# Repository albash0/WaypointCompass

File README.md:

# Waypoint Compass

**An offline GPS navigation device combining sensor integration, embedded UI, and custom PCB design.**

| Navigation interface | Module-carrier design |
| --- | --- |
|  |  |

*Left: a firmware-rendered test fixture using a public business location. Right: a CAD assembly render. Neither image is a photograph or a live navigation measurement.*

Waypoint Compass uses GPS position, a magnetometer, and accelerometer-based tilt compensation to show a target's direction and straight-line distance on a round display. It runs without a phone, Wi-Fi, or an external service. The project spans an earlier OLED prototype, a module-based color version, and a compact integrated PCB design.

A project by [albash0](https://github.com/albash0), a first-year ASEN and CTD student at CU Boulder.

[Engineering notes](docs/ENGINEERING.md) · [Hardware versions](#hardware-versions) · [Build instructions](docs/BUILD.md) · [Controls and wiring](WaypointCompass/README.md) · [Validation](VALIDATION.md)

## About the project

The core problem is making a small navigation display useful when its position, heading, and tilt inputs have different failure modes. The firmware includes calibration, sensor-frame alignment, data-age checks, and visible acquisition/lost-fix states. A target arrow is withheld when the GPS fix is missing or stale.

### My project work

| Area | Work in this project | Source and evidence |
| --- | --- | --- |
| Sensor integration | UART GPS, I²C magnetometer/accelerometer setup, magnetic calibration, frame alignment, and tilt-compensated heading | [SuperMini firmware](WaypointCompass/WaypointCompass.ino), [compact sensor mapping](WaypointCompass/CompactPCB/firmware/WaypointCompassCompact/WaypointCompassCompact.ino) |
| Navigation and interaction | Target bearing/distance, invalid-fix handling, offline nearest-target selection, diagnostics, and a round-screen interface | [Navigation logic](WaypointCompass/BottleNavigation.h), [shared UI](WaypointCompass/BottleUI.h) |
| Hardware design | Modular carrier and a compact four-layer design with onboard sensors and battery power circuitry | [Module carrier](WaypointCompass/PCB/), [C1 design and status](WaypointCompass/CompactPCB/README.md) |
| Verification and tooling | Geographic edge-case tests, real-renderer previews, three firmware builds, and a public-data update script | [Tests](WaypointCompass/tests/), [data updater](WaypointCompass/tools/update_store_list.py), [validation report](VALIDATION.md) |

The project uses TinyGPSPlus, Adafruit display libraries, and KiCad library material. Original contributors and data sources retain their licenses and credits; [third-party notices](THIRD_PARTY.md) describe those boundaries.

### Engineering decisions

- **Use gravity to account for tilt:** align the sensor frames and project magnetic/device-forward vectors onto the horizontal plane when the calibration and input checks permit.
- **Make stale input visible:** missing or outdated GPS data switches the display into an acquisition/lost-fix state.
- **Keep navigation offline:** a small flash-resident target set supports deterministic nearest-target selection without connectivity.
- **Separate software checks from hardware validation:** the compact design compiles, but its electronics still require bench bring-up.

[Read the implementation choices, tradeoffs, and proposed measurements →](docs/ENGINEERING.md)

### Status and validation

| Check | Evidence and limits |
| --- | --- |
| Navigation tests | All **19 public target points**, invalid/stale fixes, and geographic distance edge cases checked under address/undefined-behavior sanitizers. [GitHub Actions](https://github.com/albash0/WaypointCompass/actions). |
| UI | **Eight display states** rendered through actual Adafruit GFX code; examples below. |
| Firmware | SuperMini color, compact C1 color, and earlier OLED versions compiled for the public source release. |
| Module prototype | Documented as the working module-based firmware; publication did not add a new sensor/field test. |
| Compact C1 | Routed schematic/PCB and historical CAD reports are available. **Physical hardware remains unverified.** |
| Open measurements | Absolute heading accuracy, tilt/motion sensitivity, GPS acquisition time, and C1 power/charging behavior remain to be measured. |

Calibration and compilation do not establish a heading-accuracy specification. [Validation details](VALIDATION.md).

### Timeline

These dates come from retained sketch/PCB files and dated update records. They are development milestones, not an imported Git commit history.

| Date | Milestone |
| --- | --- |
| 2026-09-29 | Earliest retained OLED waypoint compass sketch: GPS, QMC5883P heading, calibration and a configurable destination. |
| 2026-09-30 | Round TFT bring-up and signal-pin diagnostics. |
| 2026-10-01 | Modular 60 × 40 mm carrier PCB design retained. |
| 2026-10-02 | Compact C1 integrated 54 × 40 mm four-layer PCB design retained, with onboard sensors and battery power circuitry. |
| 2026-10-16 | Bottle Radar update: nearest-of-19 store selection, shared UI/navigation code, GPS reception details, calibration animation and automated navigation/rendering checks. |
| 2026-11-17 | Public source preparation, removal of private waypoint defaults, and self-contained test dependencies. |

## Hardware versions

| Version | Hardware | Source |
| --- | --- | --- |
| Module-based color prototype | ESP32-S3 SuperMini, GC9A01 round TFT, QMC5883P GY-271, MPU6050 GY-521, UART GPS | [Sketch](WaypointCompass/WaypointCompass.ino), [60 × 40 mm carrier](WaypointCompass/PCB/) |
| Compact C1 prototype | ESP32-S3-MINI-1U-N4R2, LIS2MDL/LIS2DH12, USB-C, battery charging/protection; 54 × 40 mm four-layer PCB | [Firmware and board requirements](WaypointCompass/CompactPCB/README.md) — bench-unverified |
| Earlier OLED waypoint compass | ESP32-S3 SuperMini, SSD1306, QMC5883P, UART GPS; manual target | [Sketch](WaypointCompassOLED/WaypointCompassOLED.ino) |

Read the C1 battery thermistor, polarity, and charging requirements before fabrication or assembly. Supplier reference solids without a local redistribution-license record are omitted; the electrical designs remain editable.

## Interface and application mode

| Acquiring GPS | Calibration |
| --- | --- |
|  |  |

*Host-rendered test states, not live reception or calibration measurements.*

**Bottle Radar** is an application mode that selects the nearest of 19 Boulder retail liquor stores from a dated public city dataset. Manual waypoints are also supported. Distances are straight-line; the device does not provide walking routes, entrance surveys, opening hours, or live closure checks. The embedded data is a **2026-10-16 snapshot** of the [City of Boulder map](https://maps.bouldercolorado.gov/liquor-licenses/).

Private destination defaults are unset. Enter `latitude,longitude` in Serial Monitor at 115200 baud to save a personal target. On the color variants, `NEAREST` restores automatic selection. Calibration and destinations remain on the device. [Full commands, display states and prototype wiring](WaypointCompass/README.md).

## Build and test

[The build guide](docs/BUILD.md) covers the ESP32 core, display/GPS dependencies, and board-specific settings. From the repository root:

```sh
arduino-cli compile --fqbn esp32:esp32:esp32s3:CDCOnBoot=cdc,USBMode=hwcdc,FlashSize=4M --libraries libraries WaypointCompass
sh WaypointCompass/tests/run_tests.sh
```

To refresh the public target dataset, run `python3 WaypointCompass/tools/update_store_list.py`, review the result, and recompile. Both color variants must keep their copied navigation, data, and UI headers synchronized.

## License and credits

Original software, documentation and hardware designs: **GPL-2.0-or-later**, except retained third-party notices. See [LICENSE](LICENSE) and [THIRD_PARTY.md](THIRD_PARTY.md). Adafruit/KiCad material and public city data retain their original notices and applicable publisher terms.

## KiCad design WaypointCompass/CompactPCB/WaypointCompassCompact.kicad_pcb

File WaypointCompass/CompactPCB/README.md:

# Waypoint Compass Compact - C1 prototype

Open `WaypointCompassCompact.kicad_pro` in KiCad 10. The schematic, fully routed PCB and local footprint library are included. This is a new compact design; the working SuperMini/module firmware and original headered carrier remain in their existing folders.

## What is included

- 54 x 40 mm, four-layer, 1.0 mm carrier with the TFT viewing area centered at (27,20) mm.
- Existing inexpensive 7-pin GC9A01 TFT on the front, direct straight male headers and a 2.54 mm board gap.
- Two standard 6 x 6 mm front buttons on the left. Short switches may need case plungers beside the raised display.
- ESP32-S3-MINI-1U-N4R2, LIS2MDL magnetometer and LIS2DH12 accelerometer on the rear. These replace the SuperMini, GY-271 and GY-521 breakout boards. No gyroscope is needed for the current stationary tilt-compensation algorithm.
- USB-C programming and BQ24074 charging with a power path; regulated 3.3 V logic and 5 V TFT/GPS supply; battery protection and a power switch.
- Cable-connected GPS on a JST-SH 4-pin connector. Default 5 V power, selectable 3.3 V; serial signals remain 3.3 V.
- BOM, Gerbers, plated/nonplated drill files, assembly positions, firmware and board documentation.

## Battery and charging

Use a **300-1000 mAh single-cell Li-ion/LiPo intended for 4.2 V charging**. J3 is JST-PH 2-pin: **pin 1 positive, pin 2 cell negative**. Match actual plug polarity; cable colors are not authoritative.

**A separate 10k Semitec 103AT-2 battery thermistor and JST-SH 2-pin cable are required at J5.** Thermally attach the insulated thermistor to the battery. A two-wire battery does not provide this sensor. With J5 empty, charging is inhibited. Charger TS goes to J5 pin 1; J5 pin 2 is system ground. Do not replace the thermistor with a fixed resistor for normal charging.

JP2 open selects about **100 mA**. This is the default for 300-500 mAh cells. Bridge JP2 for about **250 mA** on 500-1000 mAh cells whose manufacturer permits it. For a 1000 mAh cell, use 250 mA mode; at 100 mA it can exceed the charger's timer. Timer is about 9.53 hours nominal, with IC tolerance approximately 7.15-11.92 hours. USB input mode is fixed at 500 mA; the power path reduces charge current when the running load needs the available input current. Switching the device off disables the two regulators while USB charging remains available.

Cell-negative and system GND are separate nets joined by the protection MOSFETs. **Do not wire J3 pin 2 to a system-GND test pad**, because that bypasses protection.

## Build and prototype verification

C1 is a **bench-unverified prototype**. KiCad ERC: 0 violations. PCB DRC: 0 violations, 0 unconnected items and 0 schematic parity issues with the supplied rules; the reports list configured ignored checks. Firmware compiles with ESP32 Arduino core 3.3.8. These checks establish file consistency, not successful hardware operation or charging certification.

Use SMT assembly/reflow for the LGA, QFN, SON and WSON packages. Most passives are 0603; R19/R20 are 0402. Hand solder the front buttons, TFT header and rear JST-PH battery connector. Supply the assembler with BOM, position CSV, native project and component orientation information. Confirm actual MPN availability and permitted substitutions at ordering.

Before using the battery charger, verify power rails, charge current, NTC response, protection behavior, temperature and sensors on the bench. Keep the battery and its cable away from the magnetometer; recalibrate in the final assembled enclosure and check heading while charging.

## Firmware

**2026-10-16 update:** Bottle Radar now selects the nearest of 19 city-listed Boulder retail liquor stores. See `firmware/README.md` for current UI and commands; the build guide describes the original firmware.

Sketch: `firmware/WaypointCompassCompact/WaypointCompassCompact.ino`.

Arduino IDE board: ESP32S3 Dev Module; 4 MB flash; QSPI PSRAM; Hardware CDC/JTAG USB; USB CDC On Boot enabled. Install TinyGPSPlus, Adafruit GFX, Adafruit GC9A01A and their Library Manager dependencies.

- Default mode: nearest city-listed Boulder liquor store. Manual coordinates remain available over USB.
- First startup runs 10-second 3D calibration; rotate the complete device around all axes. Valid calibration is saved across resets.
- CAL button repeats calibration. Holding CAL while resetting enters the USB ROM bootloader; release CAL after entering the bootloader.
- ACTION toggles GPS diagnostics. Serial commands at 115200: `NEAREST`, `STORES`, `DETAILS`, `STATUS`, `NMEA`, `CAL`, `CLEAR`, or `latitude,longitude`.
- GPS defaults to 9600 baud. GPIO44 receives GPS TX; GPIO43 transmits to GPS RX.
- Compact sensor mapping matches rear-mounted C1 footprints. Verify +Z gravity is approximately +1 g with the screen face up, and check compass direction/tilt on the first board.
- Battery voltage in Serial STATUS is an ADC estimate, not a percentage gauge.

Compile command (with arduino-cli installed):

```sh
arduino-cli compile --fqbn esp32:esp32:esp32s3:CDCOnBoot=cdc,USBMode=hwcdc,FlashSize=4M,PSRAM=enabled firmware/WaypointCompassCompact
```

## Public source files

Native KiCad schematic, routed PCB, local symbols/footprints, BOM and unpacked fabrication outputs are included. Supplier 3D references, derived assembly solids, historical ZIPs, prebuilt firmware and local CAD history are omitted. Model paths may refer to omitted visualization assets; they do not affect copper or fabrication. Use the schematic and BOM to review the design.

The native files are the design authority. Development scripts are retained as references; running `build_compact.py --board` regenerates an unrouted board and overwrites the routed layout. Work in a separate copy before regenerating.

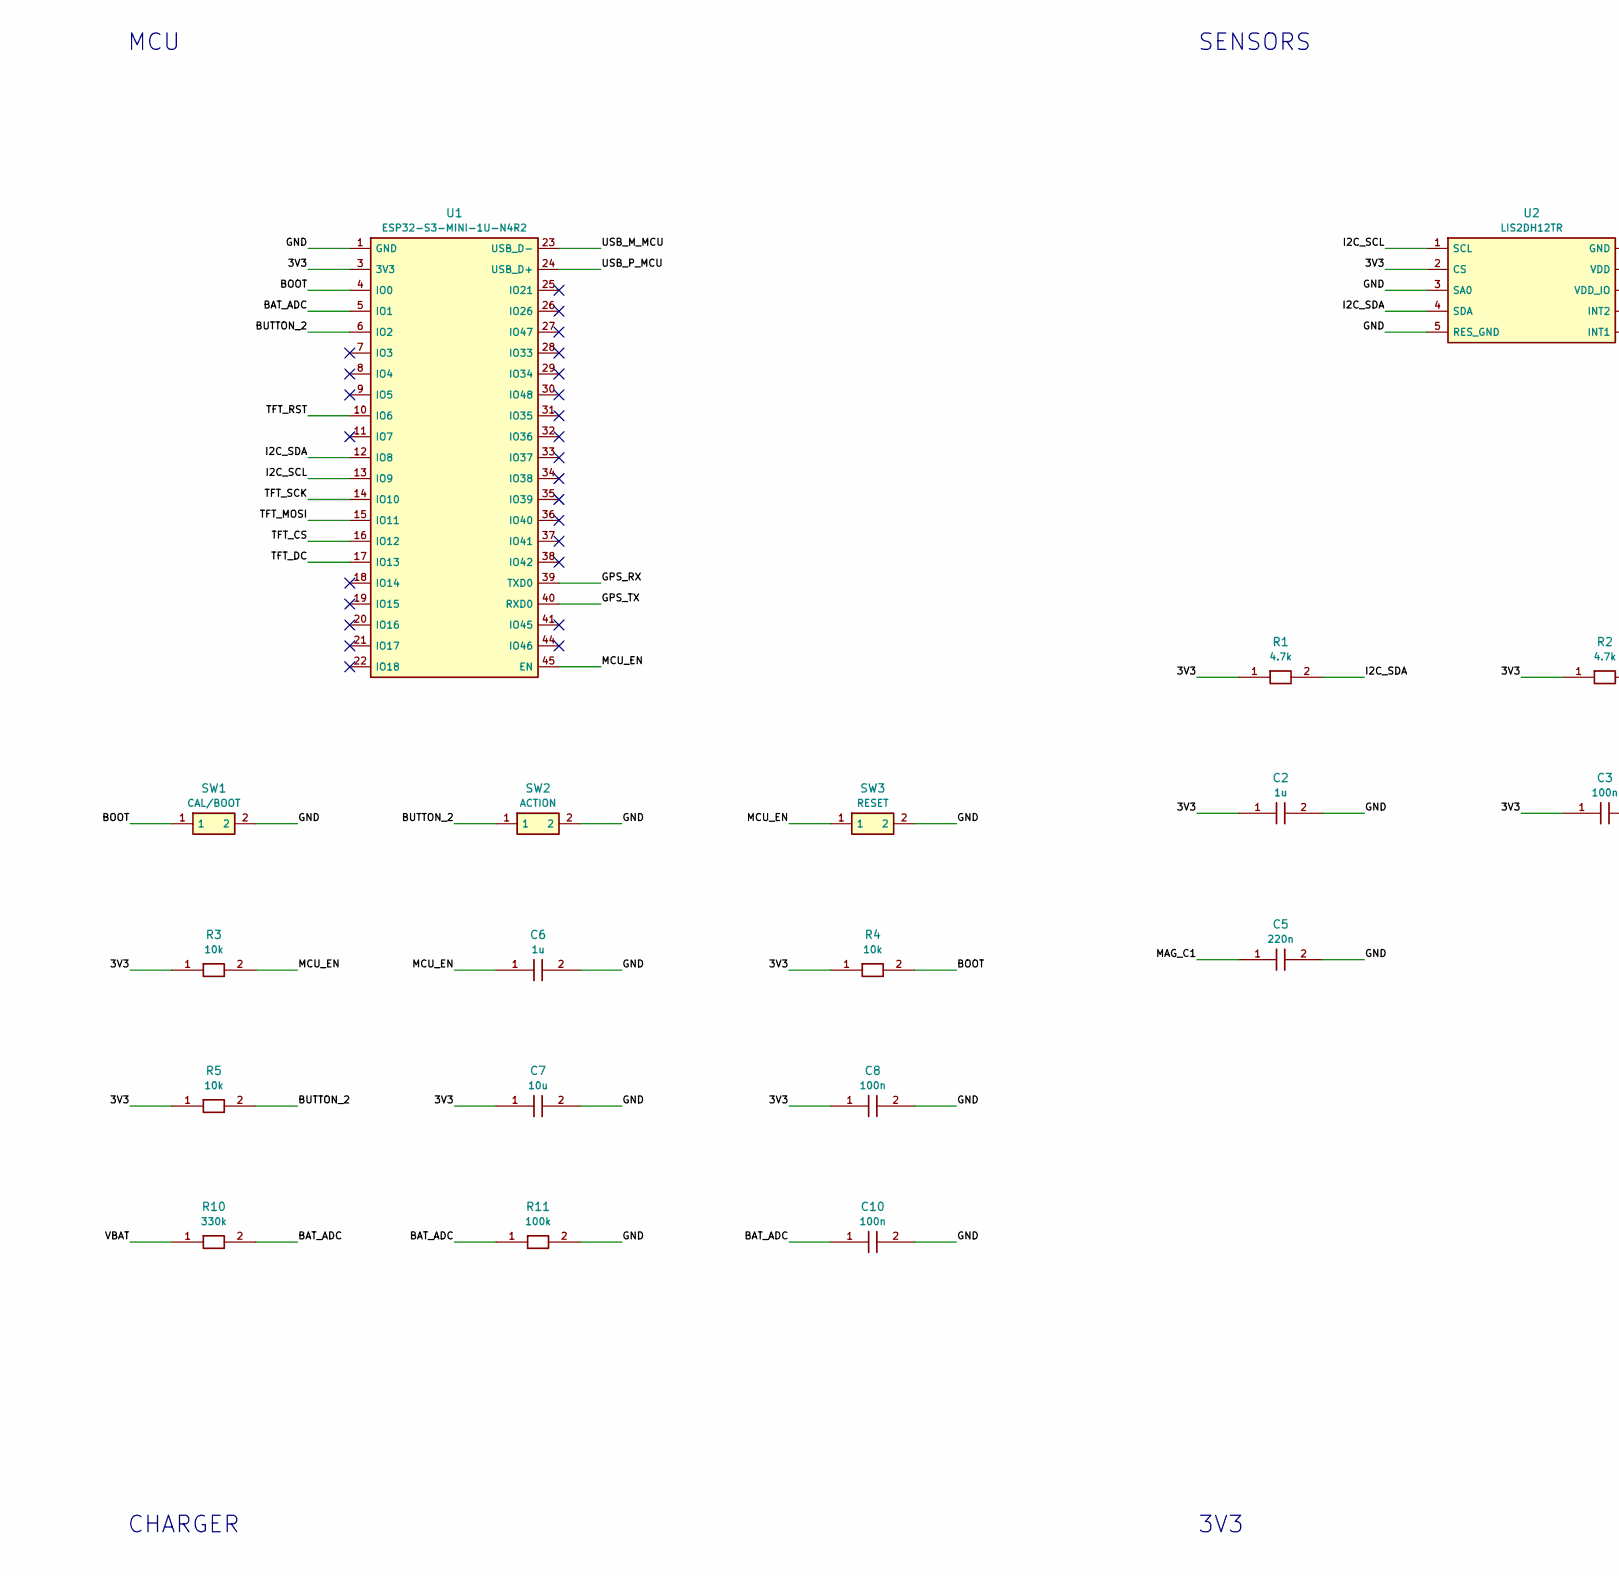
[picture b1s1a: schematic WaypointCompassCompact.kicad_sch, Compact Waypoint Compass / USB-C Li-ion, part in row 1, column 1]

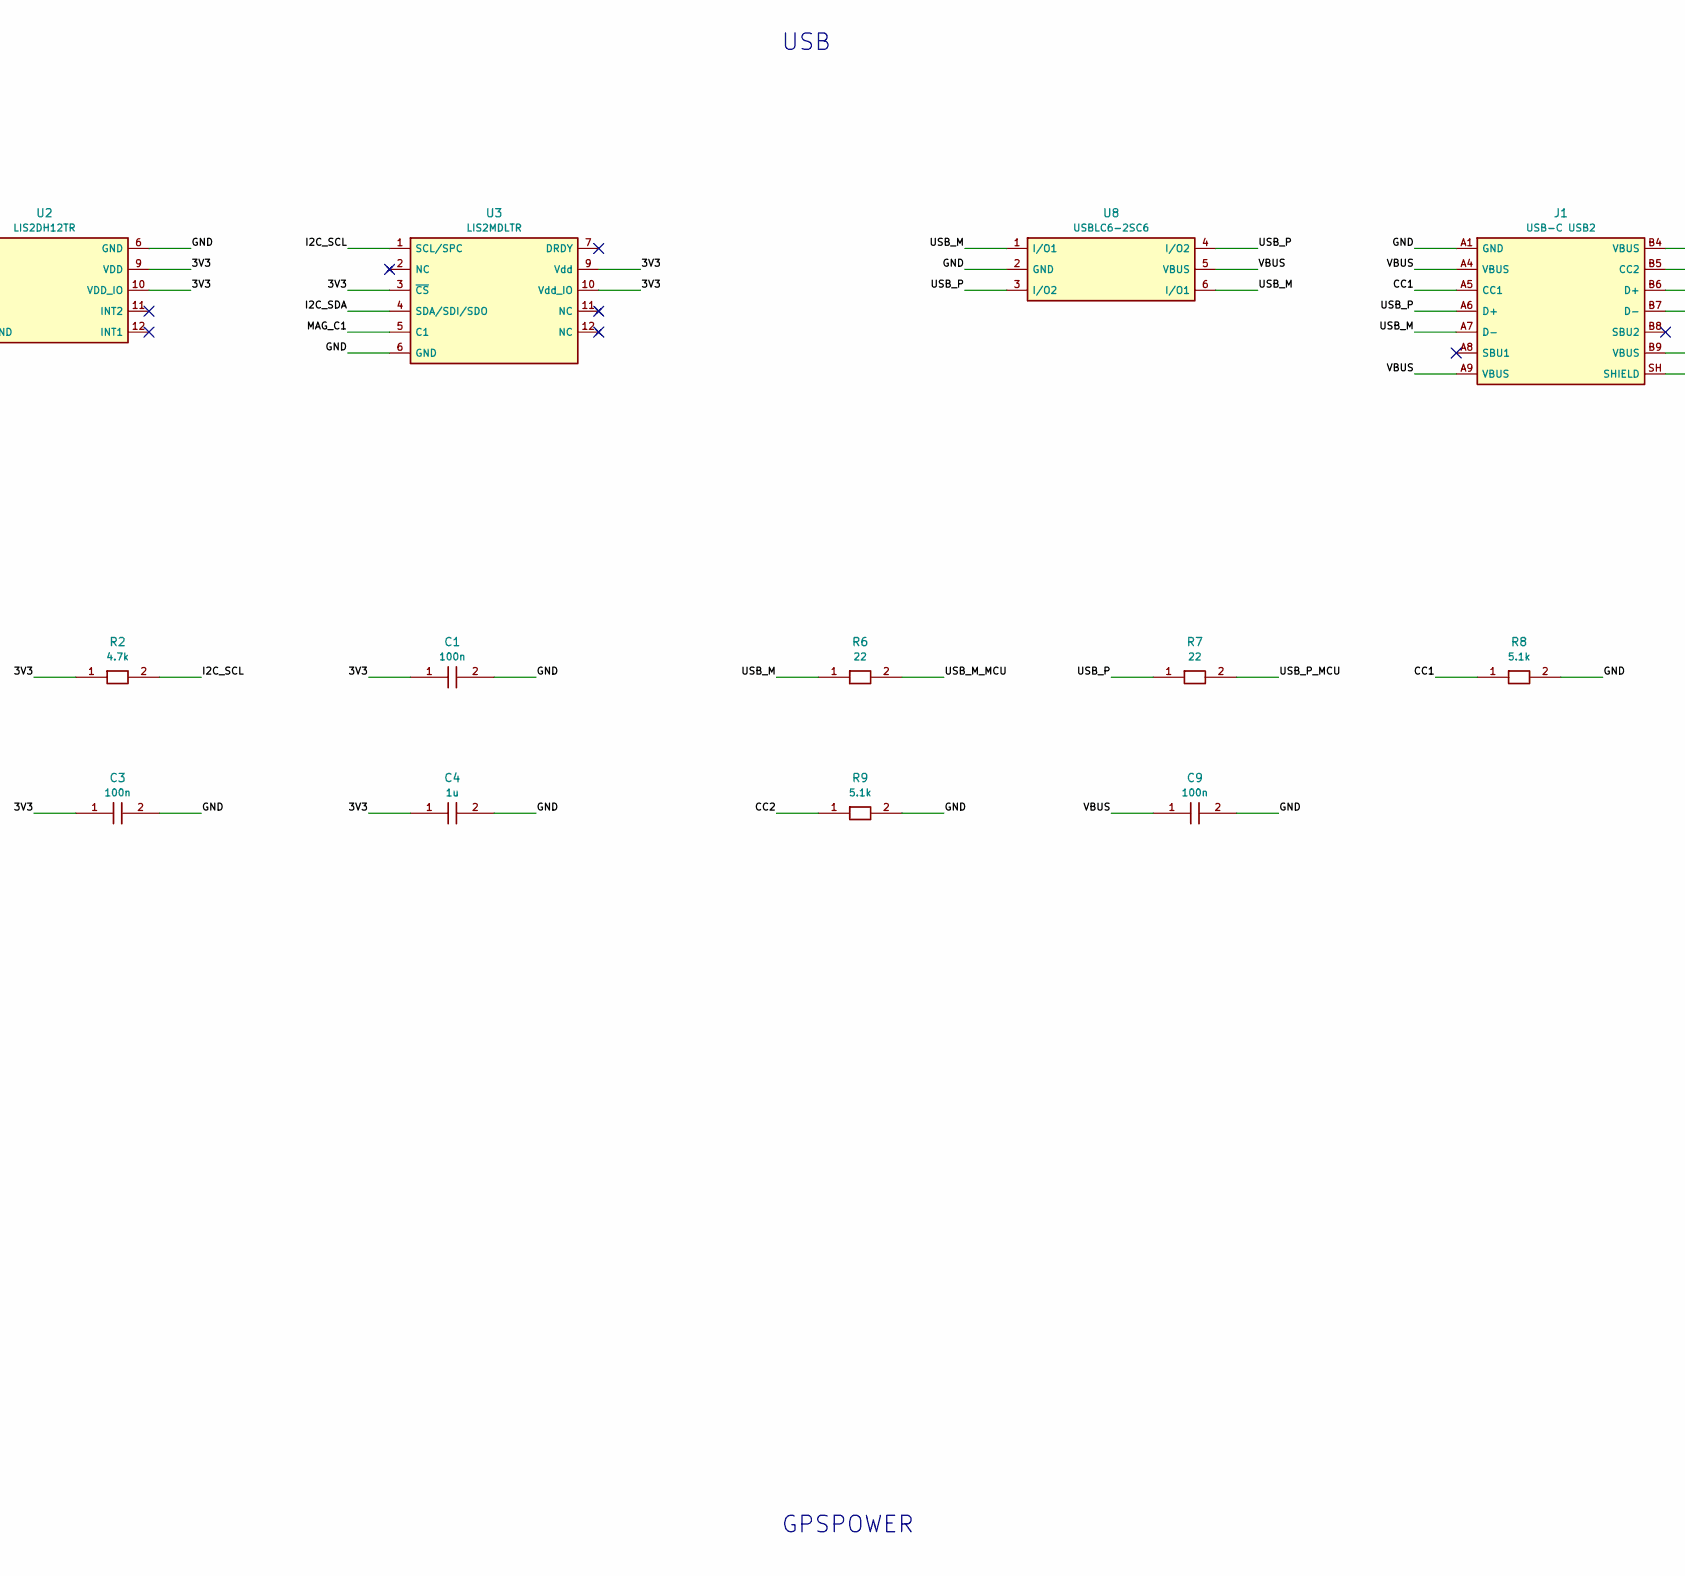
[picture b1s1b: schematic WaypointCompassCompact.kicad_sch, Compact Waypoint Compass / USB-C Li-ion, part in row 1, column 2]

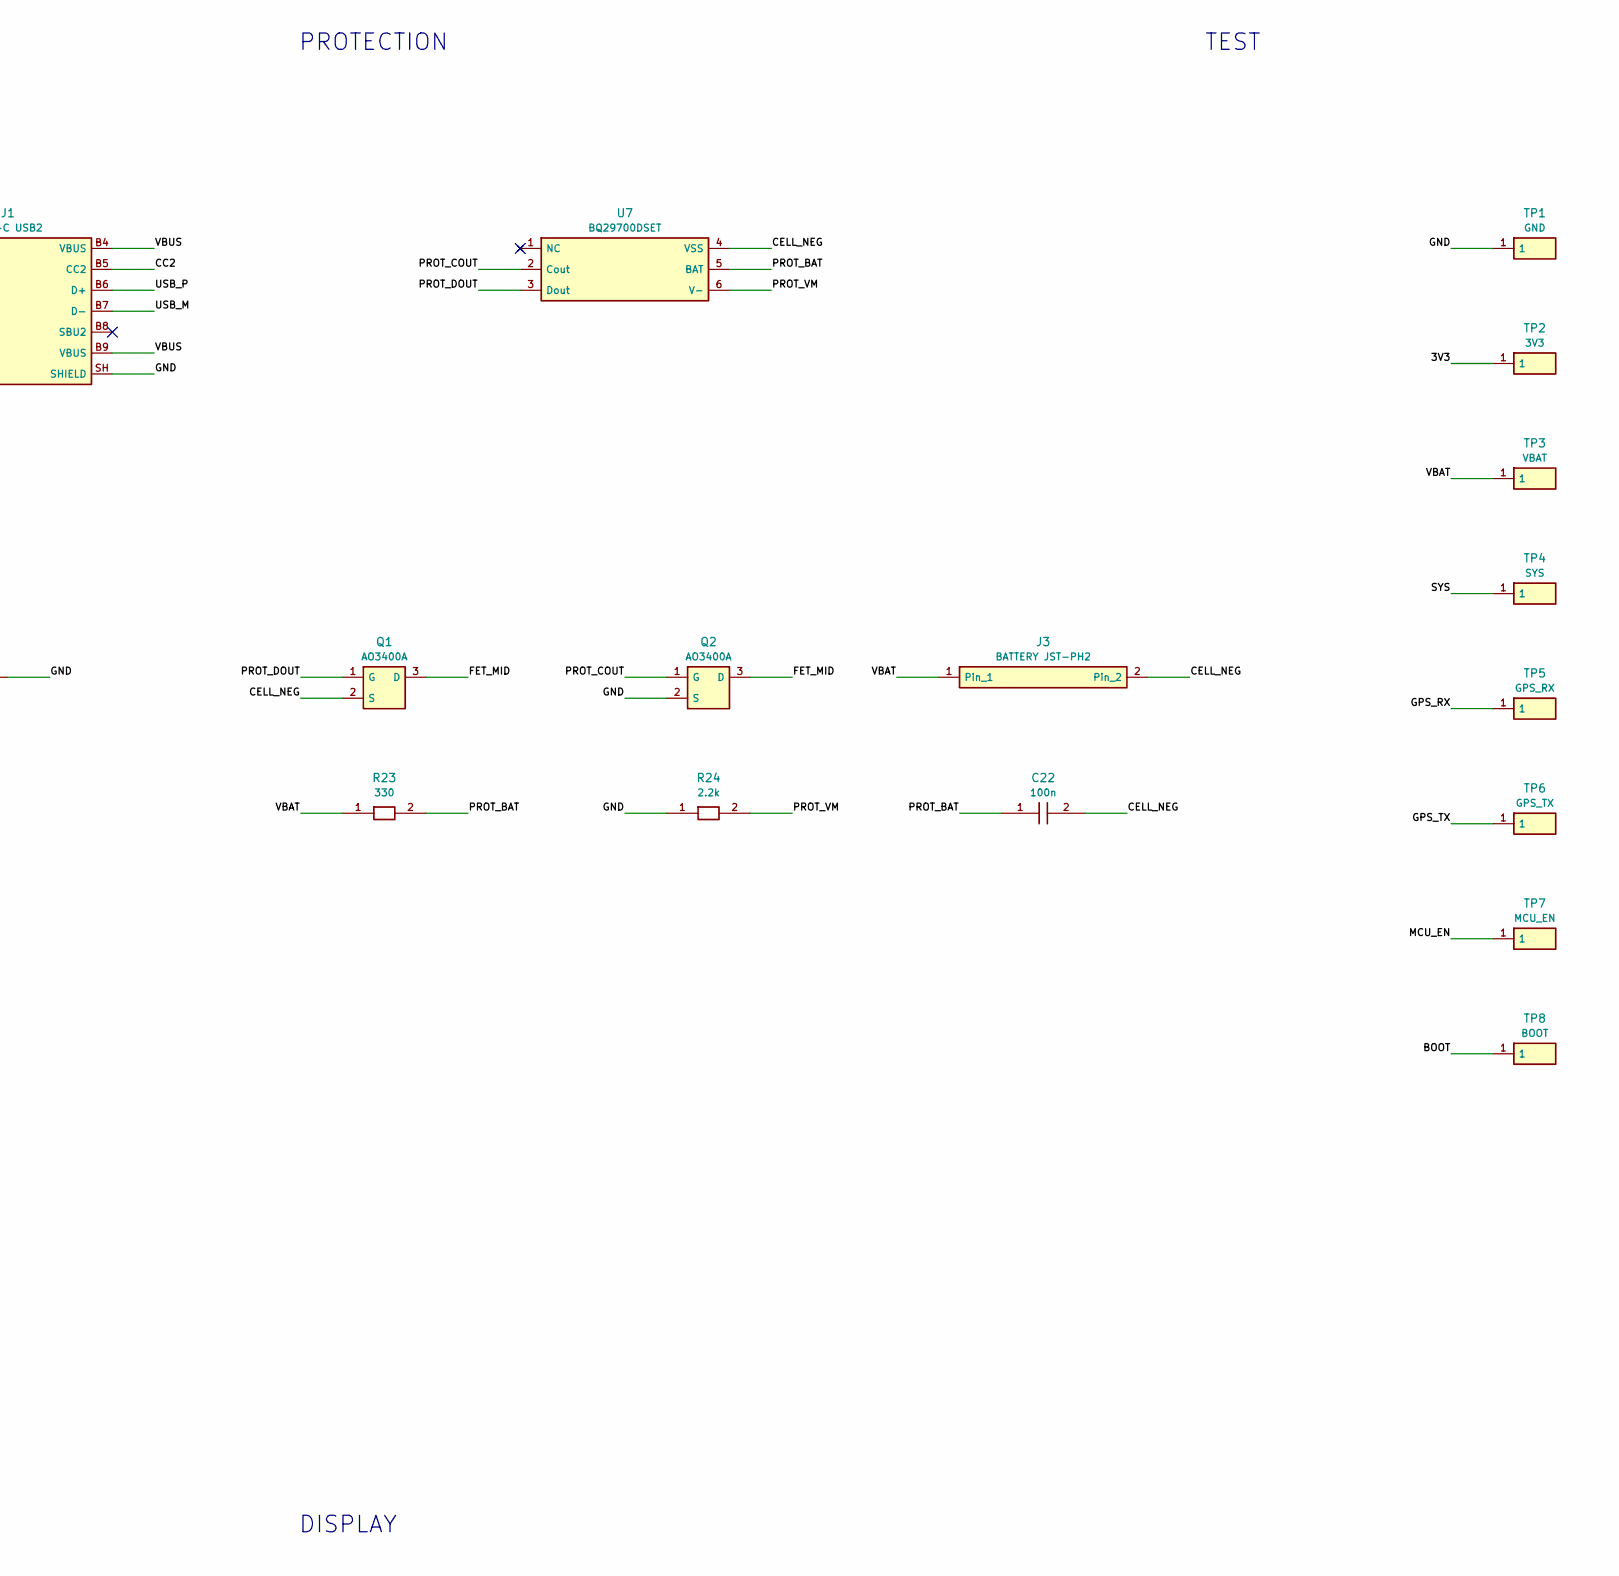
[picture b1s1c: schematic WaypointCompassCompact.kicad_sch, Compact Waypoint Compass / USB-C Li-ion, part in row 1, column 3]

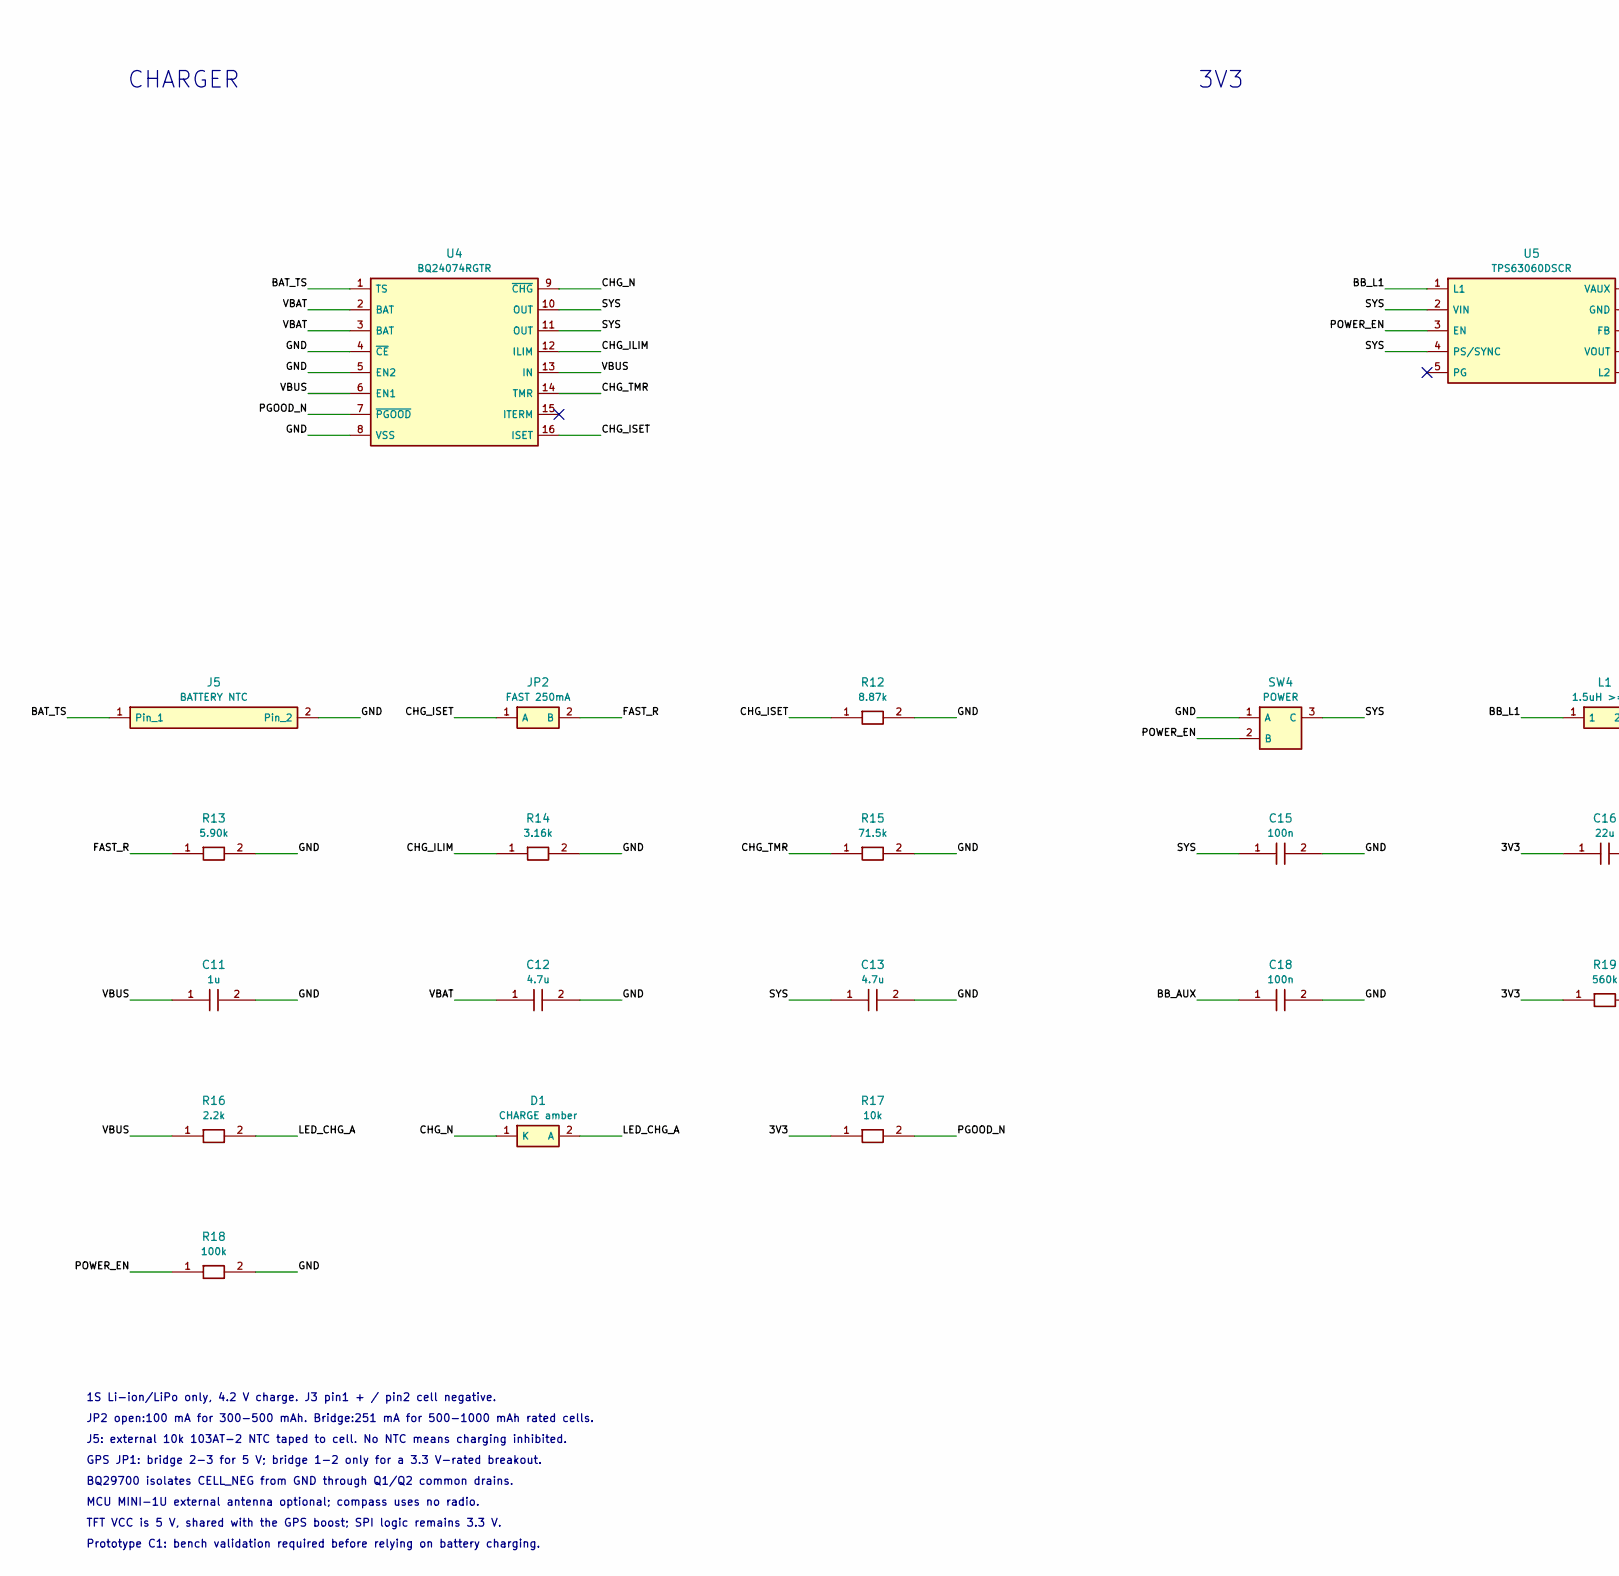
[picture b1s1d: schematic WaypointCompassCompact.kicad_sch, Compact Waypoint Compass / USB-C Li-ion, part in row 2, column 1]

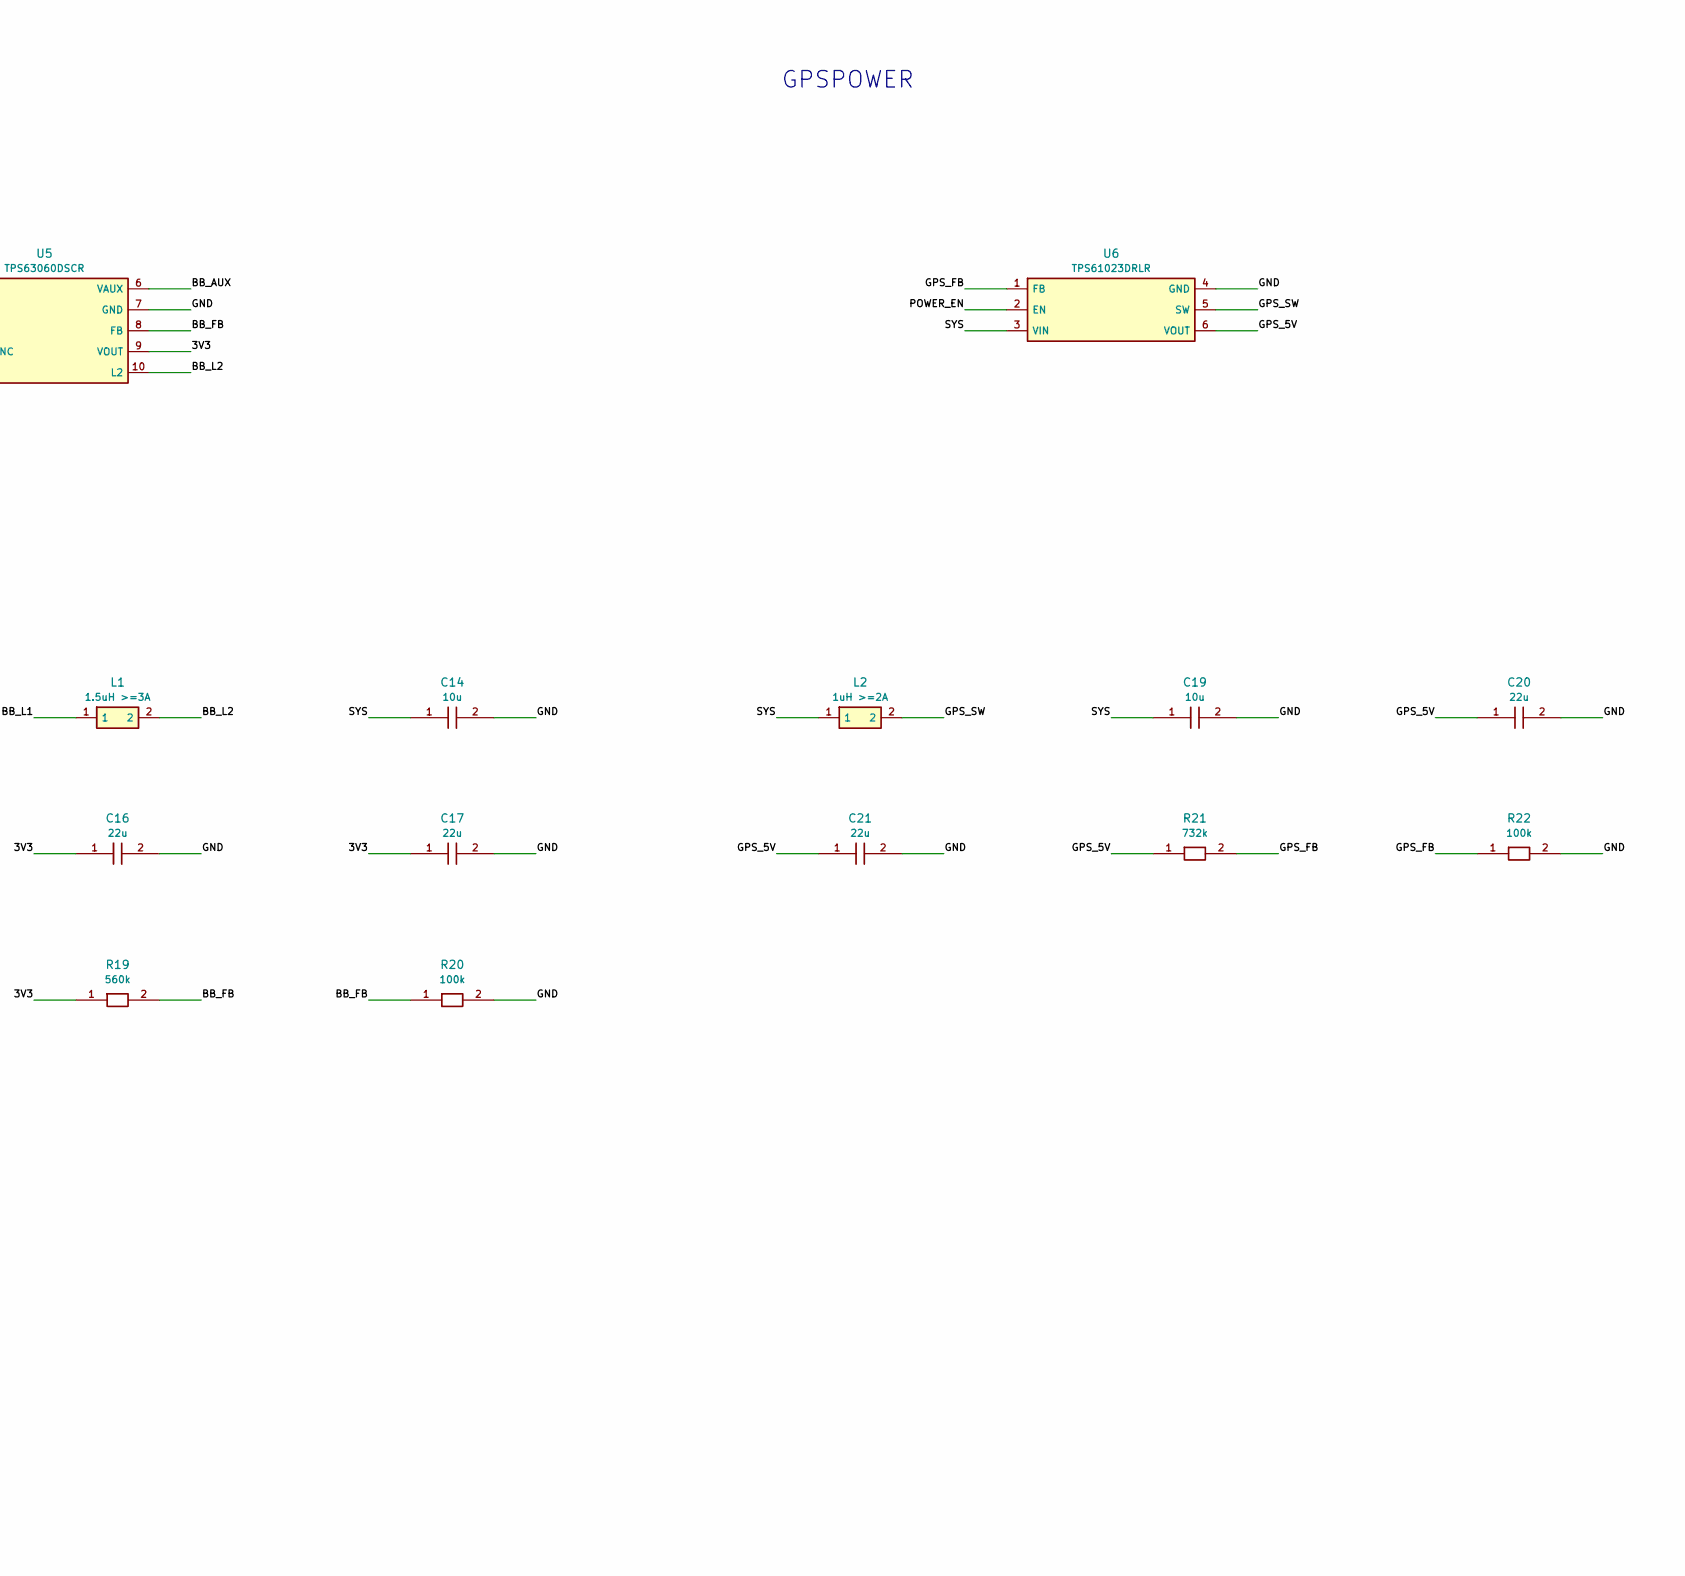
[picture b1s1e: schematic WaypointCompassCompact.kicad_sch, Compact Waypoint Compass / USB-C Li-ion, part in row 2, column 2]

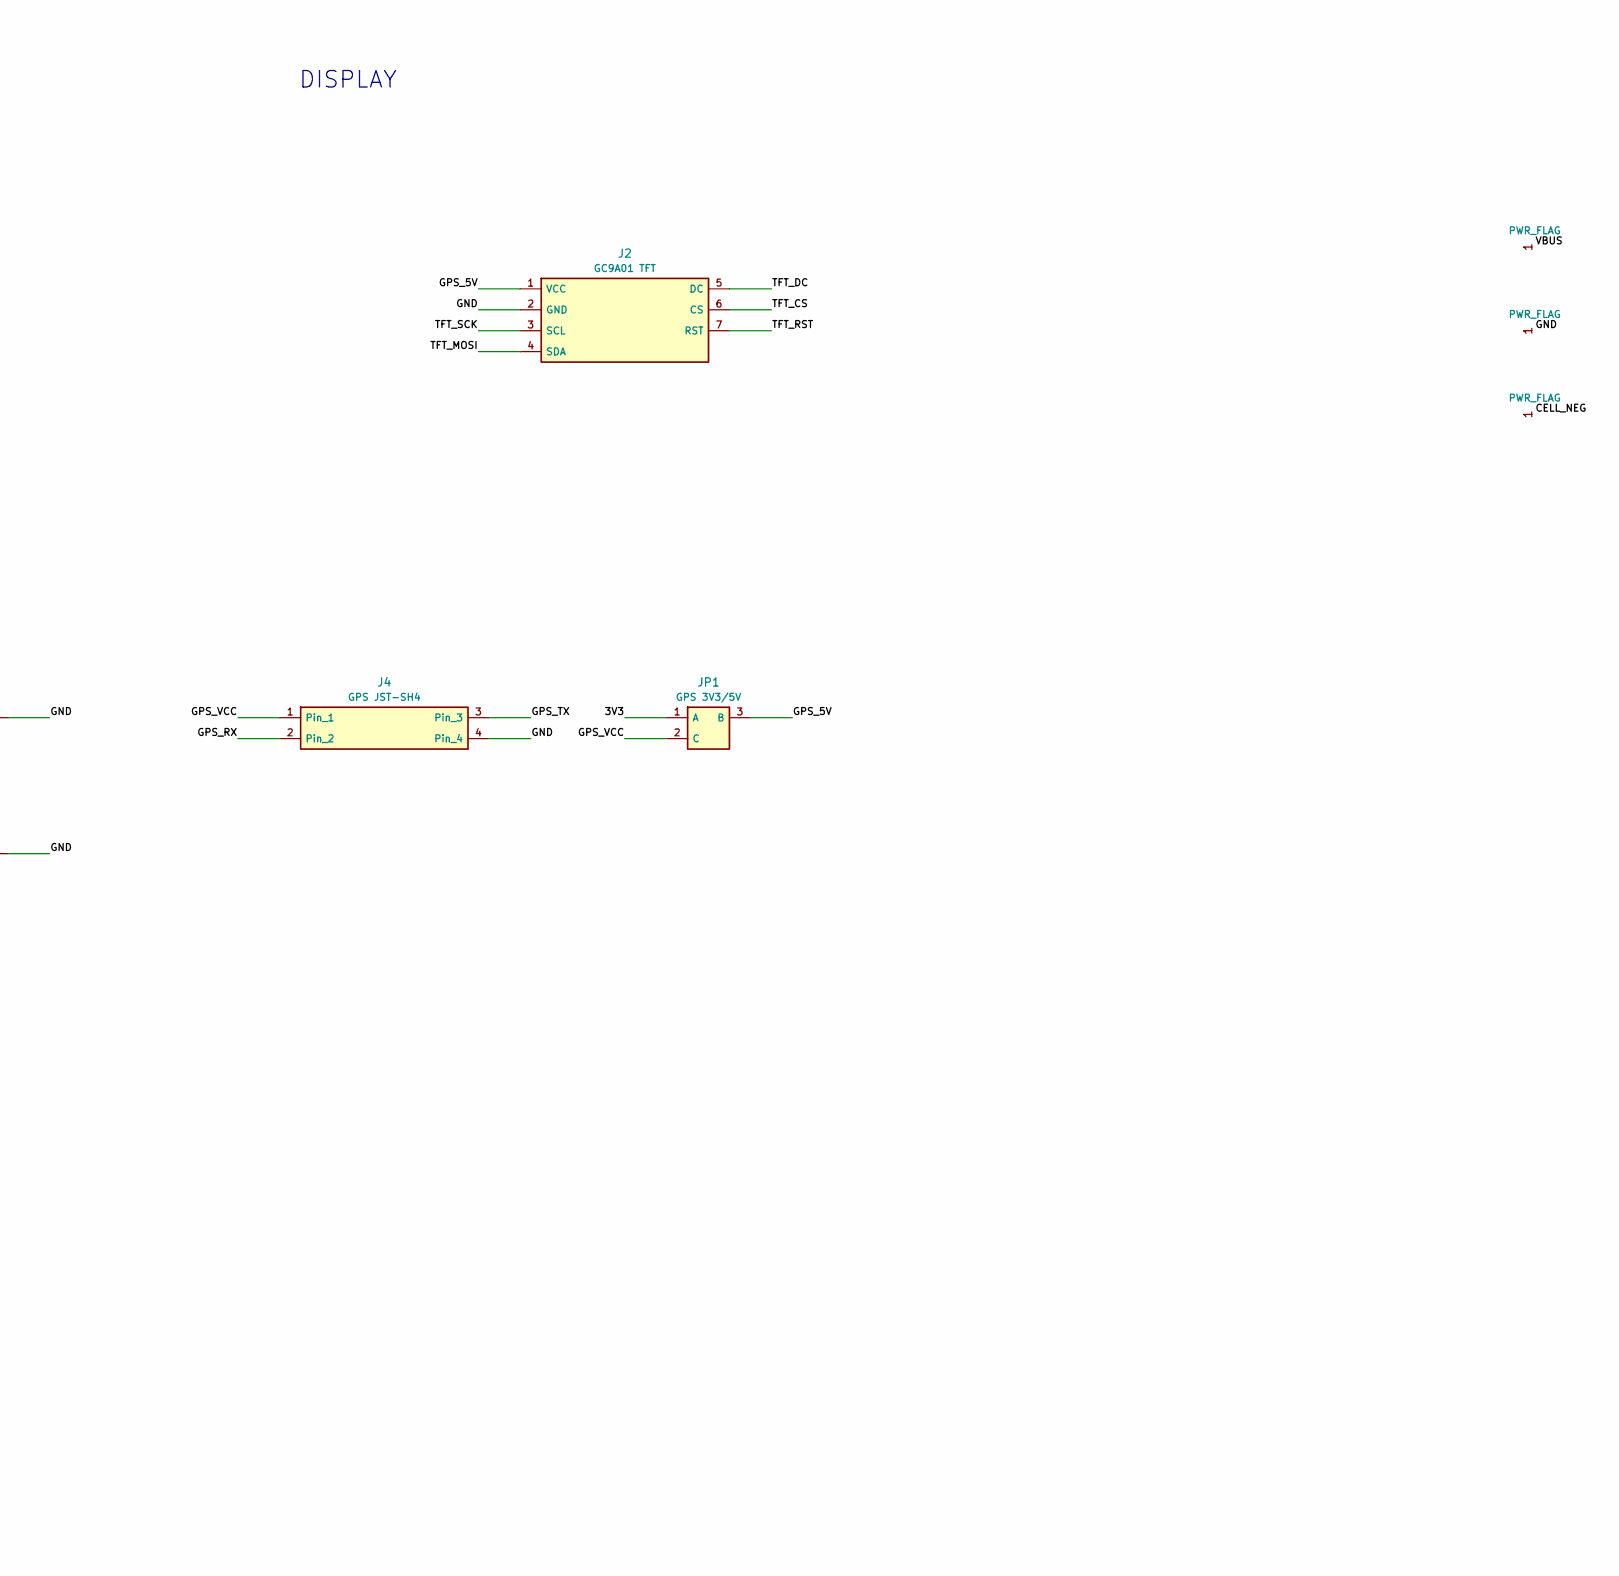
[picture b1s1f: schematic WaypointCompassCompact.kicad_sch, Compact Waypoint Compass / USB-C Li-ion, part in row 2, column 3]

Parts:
C1, C3, C8, C9, C10, C15, C18, C22: 100n; C_0603_1608Metric
C2, C4, C6, C11: 1u; C_0603_1608Metric
C5: 220n; C_0603_1608Metric
C7, C14, C19: 10u; C_0805_2012Metric
C12, C13: 4.7u; C_0603_1608Metric
C16, C17, C20, C21: 22u; C_0805_2012Metric
D1: CHARGE amber; LED_0603_1608Metric
J1: USB-C USB2; USB_C_Receptacle_HRO_TYPE-C-31-M-12
J2: GC9A01 TFT; GC9A01_TFT_Socket
J3: BATTERY JST-PH2; JST_PH_S2B-PH-K_1x02_P2.00mm_Horizontal
J4: GPS JST-SH4; JST_SH_SM04B-SRSS-TB_1x04-1MP_P1.00mm_Horizontal
J5: BATTERY NTC; JST_SH_SM02B-SRSS-TB_1x02-1MP_P1.00mm_Horizontal
JP1: GPS 3V3/5V; SolderJumper-3_P1.3mm_Open_Pad1.0x1.5mm
JP2: FAST 250mA; SolderJumper-2_P1.3mm_Open_Pad1.0x1.5mm
L1: 1.5uH >=3A; L_Vishay_IFSC-1515AH_4x4x1.8mm
L2: 1uH >=2A; L_Vishay_IHLP-1212
Q1, Q2: AO3400A; SOT-23
R1, R2: 4.7k; R_0603_1608Metric
R3, R4, R5, R17: 10k; R_0603_1608Metric
R6, R7: 22; R_0603_1608Metric
R8, R9: 5.1k; R_0603_1608Metric
R10: 330k; R_0603_1608Metric
R11, R18, R22: 100k; R_0603_1608Metric
R12: 8.87k; R_0603_1608Metric
R13: 5.90k; R_0603_1608Metric
R14: 3.16k; R_0603_1608Metric
R15: 71.5k; R_0603_1608Metric
R16, R24: 2.2k; R_0603_1608Metric
R19: 560k; R_0402_1005Metric
R20: 100k; R_0402_1005Metric
R21: 732k; R_0603_1608Metric
R23: 330; R_0603_1608Metric
SW1: CAL/BOOT; SW_PUSH_6mm
SW2: ACTION; SW_PUSH_6mm
SW3: RESET; SW_SPST_TL3342
SW4: POWER; SW_SPDT_CK_JS102011SAQN
TP1: GND; TestPoint_Pad_D1.0mm
TP2: 3V3; TestPoint_Pad_D1.0mm
TP3: VBAT; TestPoint_Pad_D1.0mm
TP4: SYS; TestPoint_Pad_D1.0mm
TP5: GPS_RX; TestPoint_Pad_D1.0mm
TP6: GPS_TX; TestPoint_Pad_D1.0mm
TP7: MCU_EN; TestPoint_Pad_D1.0mm
TP8: BOOT; TestPoint_Pad_D1.0mm
U1: ESP32-S3-MINI-1U-N4R2; ESP32-S2-MINI-1U
U2: LIS2DH12TR; LGA-12_2x2mm_P0.5mm
U3: LIS2MDLTR; LGA-12_2x2mm_P0.5mm
U4: BQ24074RGTR; VQFN-16-1EP_3x3mm_P0.5mm_EP1.6x1.6mm
U5: TPS63060DSCR; Texas_S-PWSON-N10
U6: TPS61023DRLR; SOT-563
U7: BQ29700DSET; WSON-6_1.5x1.5mm_P0.5mm
U8: USBLC6-2SC6; SOT-23-6

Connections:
/3V3: C1.1, C2.1, C3.1, C4.1, C7.1, C8.1, C16.1, C17.1, JP1.1 (A), R1.1, R2.1, R3.1, R4.1, R5.1, R17.1, R19.1, TP2.1, U1.3 (3V3), U2.2 (CS), U2.9 (VDD), U2.10 (VDD_IO), U3.3 (~CS), U3.9 (Vdd), U3.10 (Vdd_IO), U5.9 (VOUT)
/BAT_ADC: C10.1, R10.2, R11.1, U1.5 (IO1)
/BAT_TS: J5.1, U4.1 (TS)
/BB_AUX: C18.1, U5.6 (VAUX)
/BB_FB: R19.2, R20.1, U5.8 (FB)
/BB_L1: L1.1, U5.1 (L1)
/BB_L2: L1.2, U5.10 (L2)
/BOOT: R4.2, SW1.1, TP8.1, U1.4 (IO0)
/BUTTON_2: R5.2, SW2.1, U1.6 (IO2)
/CC1: J1.A5 (CC1), R8.1
/CC2: J1.B5 (CC2), R9.1
/CELL_NEG: C22.2, J3.2, Q1.2 (S), U7.4 (VSS)
/CHG_ILIM: R14.1, U4.12 (ILIM)
/CHG_ISET: JP2.1 (A), R12.1, U4.16 (ISET)
/CHG_N: D1.1 (K), U4.9 (~CHG)
/CHG_TMR: R15.1, U4.14 (TMR)
/FAST_R: JP2.2 (B), R13.1
/FET_MID: Q1.3 (D), Q2.3 (D)
/GND: C1.2, C2.2, C3.2, C4.2, C5.2, C6.2, C7.2, C8.2, C9.2, C10.2, C11.2, C12.2, C13.2, C14.2, C15.2, C16.2, C17.2, C18.2, C19.2, C20.2, C21.2, J1.A1 (GND), J1.A12 (GND), J1.B1 (GND), J1.B12 (GND), J1.SH (SHIELD), J2.2 (GND), J4.4, J5.2, Q2.2 (S), R8.2, R9.2, R11.2, R12.2, R13.2, R14.2, R15.2, R18.2, R20.2, R22.2, R24.1, SW1.2, SW2.2, SW3.2, SW4.1 (A), TP1.1, U1.1 (GND), U1.2 (GND), U1.42 (GND), U1.43 (GND), U1.46 (GND), U1.47 (GND), U1.48 (GND), U1.49 (GND), U1.50 (GND), U1.51 (GND), U1.52 (GND), U1.53 (GND), U1.54 (GND), U1.55 (GND), U1.56 (GND), U1.57 (GND), U1.58 (GND), U1.59 (GND), U1.60 (GND), U1.61 (GND), U1.62 (GND), U1.63 (GND), U1.64 (GND), U1.65 (GND), U2.3 (SA0), U2.5 (RES_GND), U2.6 (GND), U2.7 (GND), U2.8 (GND), U3.6 (GND), U3.8 (GND), U4.4 (~CE), U4.5 (EN2), U4.8 (VSS), U4.17 (VSS), U5.7 (GND), U5.11 (PGND), U6.4 (GND), U8.2 (GND)
/GPS_5V: C20.1, C21.1, J2.1 (VCC), JP1.3 (B), R21.1, U6.6 (VOUT)
/GPS_FB: R21.2, R22.1, U6.1 (FB)
/GPS_RX: J4.2, TP5.1, U1.39 (TXD0)
/GPS_SW: L2.2, U6.5 (SW)
/GPS_TX: J4.3, TP6.1, U1.40 (RXD0)
/GPS_VCC: J4.1, JP1.2 (C)
/I2C_SCL: R2.2, U1.13 (IO9), U2.1 (SCL), U3.1 (SCL/SPC)
/I2C_SDA: R1.2, U1.12 (IO8), U2.4 (SDA), U3.4 (SDA/SDI/SDO)
/LED_CHG_A: D1.2 (A), R16.2
/MAG_C1: C5.1, U3.5 (C1)
/MCU_EN: C6.1, R3.2, SW3.1, TP7.1, U1.45 (EN)
/PGOOD_N: R17.2, U4.7 (~PGOOD)
/POWER_EN: R18.1, SW4.2 (B), U5.3 (EN), U6.2 (EN)
/PROT_BAT: C22.1, R23.2, U7.5 (BAT)
/PROT_COUT: Q2.1 (G), U7.2 (Cout)
/PROT_DOUT: Q1.1 (G), U7.3 (Dout)
/PROT_VM: R24.2, U7.6 (V-)
/SYS: C13.1, C14.1, C15.1, C19.1, L2.1, SW4.3 (C), TP4.1, U4.10 (OUT), U4.11 (OUT), U5.2 (VIN), U5.4 (PS/SYNC), U6.3 (VIN)
/TFT_CS: J2.6 (CS), U1.16 (IO12)
/TFT_DC: J2.5 (DC), U1.17 (IO13)
/TFT_MOSI: J2.4 (SDA), U1.15 (IO11)
/TFT_RST: J2.7 (RST), U1.10 (IO6)
/TFT_SCK: J2.3 (SCL), U1.14 (IO10)
/USB_M: J1.A7 (D-), J1.B7 (D-), R6.1, U8.1 (I/O1), U8.6 (I/O1)
/USB_M_MCU: R6.2, U1.23 (USB_D-)
/USB_P: J1.A6 (D+), J1.B6 (D+), R7.1, U8.3 (I/O2), U8.4 (I/O2)
/USB_P_MCU: R7.2, U1.24 (USB_D+)
/VBAT: C12.1, J3.1, R10.1, R23.1, TP3.1, U4.2 (BAT), U4.3 (BAT)
/VBUS: C9.1, C11.1, J1.A4 (VBUS), J1.A9 (VBUS), J1.B4 (VBUS), J1.B9 (VBUS), R16.1, U4.6 (EN1), U4.13 (IN), U8.5 (VBUS)

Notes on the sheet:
MCU
SENSORS
USB
PROTECTION
CHARGER
3V3
GPSPOWER
DISPLAY
TEST
1S Li-ion/LiPo only, 4.2 V charge. J3 pin1 + / pin2 cell negative.
JP2 open:100 mA for 300-500 mAh. Bridge:251 mA for 500-1000 mAh rated cells.
J5: external 10k 103AT-2 NTC taped to cell. No NTC means charging inhibited.
GPS JP1: bridge 2-3 for 5 V; bridge 1-2 only for a 3.3 V-rated breakout.
BQ29700 isolates CELL_NEG from GND through Q1/Q2 common drains.
MCU MINI-1U external antenna optional; compass uses no radio.
TFT VCC is 5 V, shared with the GPS boost; SPI logic remains 3.3 V.
Prototype C1: bench validation required before relying on battery charging.
